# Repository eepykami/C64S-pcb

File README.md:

# C64S-pcb
PCB to connect a C64 Datasette to an LPT port.

Credit to https://markus.brenner.de/adapter/index.html and https://www.commodore-info.com/article/item/tape_transfer/en/desktop

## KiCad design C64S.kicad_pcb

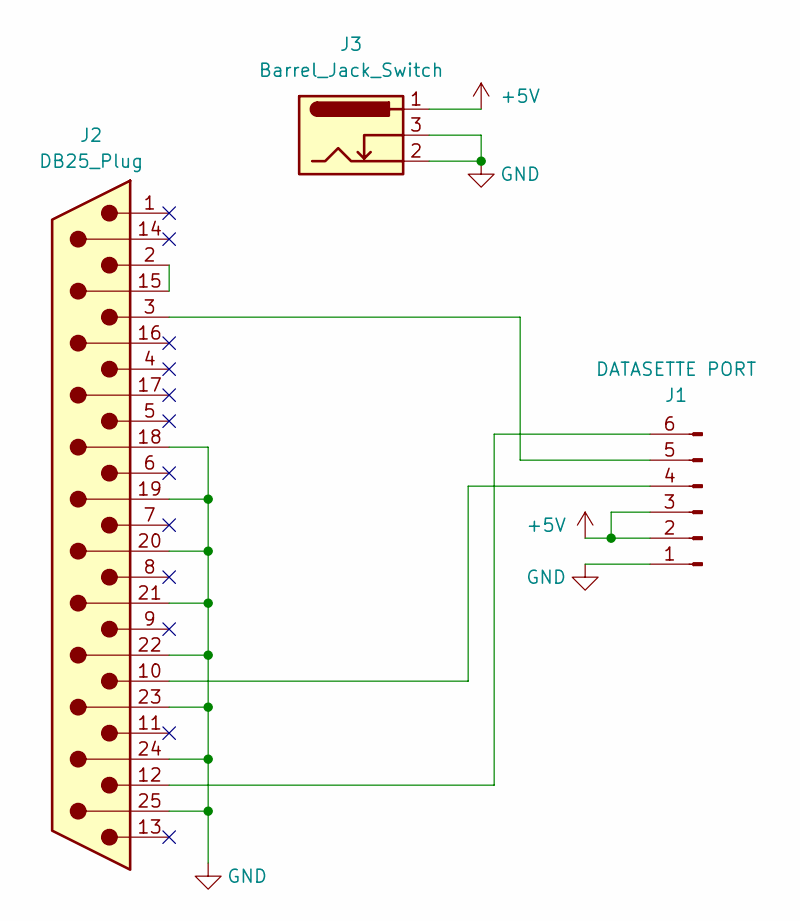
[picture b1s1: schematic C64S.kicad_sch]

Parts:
J1: DATASETTE PORT; C64_Datasette_Connector
J2: DB25_Plug; DSUB-25_Male_EdgeMount_P2.77mm; LCSC C75745
J3: Barrel_Jack_Switch; BarrelJack_Horizontal; LCSC C16214

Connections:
+5V: J1.2 (5V), J1.3 (Motor), J3.1
GND: J1.1 (GND), J2.18, J2.19, J2.20, J2.21, J2.22, J2.23, J2.24, J2.25, J3.2, J3.3
unnamed: J1.4 (Read), J2.10
unnamed: J1.6 (Sense), J2.12
unnamed: J1.5 (Write), J2.3
unnamed: J2.2, J2.15

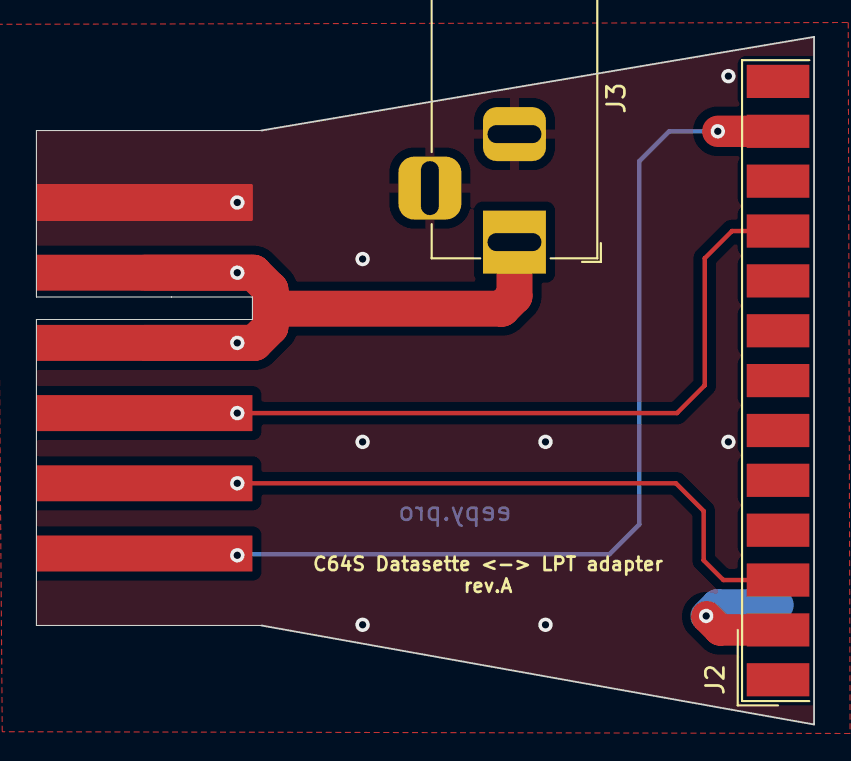
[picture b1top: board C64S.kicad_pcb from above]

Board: 2 copper layers, 43.2 x 38.2 mm, 3 parts (1 on the bottom side), 6 nets.

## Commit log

2024-03-06 Add .gitignore
2024-03-06 Add screenshots
2024-08-11 Add LCSC part no's, website address and update schematic
